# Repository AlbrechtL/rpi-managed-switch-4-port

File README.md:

# 4-Port Managed Switch

An open-source 4-port gigabit managed switch HAT based on a Raspberry Pi with OpenWrt support.

**Disclaimer:** This is an ongoing project where some features are not working, and some hardware bugs may exist.

## Features
* 4 Gigabit Ethernet RJ45 ports  
* Supports Raspberry Pi 1–5 (including Raspberry Pi Zero 1–2)  
  - Tested with a Raspberry Pi Zero 1  
  - Raspberry Pi 5 is not working with OpenWrt due to this [issue](https://github.com/openwrt/openwrt/issues/18034)  
* Works with a [custom OpenWrt](https://github.com/AlbrechtL/rpi-managed-switch-openwrt/tree/rpi_managed_switch)  
* Supported by Linux [Distributed Switch Architecture (DSA)](https://www.kernel.org/doc/Documentation/networking/dsa/dsa.txt)  
* VLAN support
* Switching hardware offloading support 
* Hardware design in KiCad
* Ready for JLCPCB production
  - Using a much as possible basic parts to lower the assembling costs

## Software Status

The hardware works with a adapted OpenWrt: https://github.com/AlbrechtL/openwrt/tree/rpi_managed_switch

I added the following to OpenWrt:  
* Device tree overlays for DSA
* Enabled the ENC28J60 driver 
* Added a small patch to enable the ENC28J60 for DSA  
* Added detection of DSA in the first boot scripts so that OpenWrt uses the switch  

See the differences:  
https://github.com/openwrt/openwrt/compare/main...AlbrechtL:openwrt:rpi_managed_switch  

Communication with the RTL8367S switch chip uses Linux DSA. There is also an OpenWrt-specific driver (`drivers/net/phy/rtl8367b.c`) for OpenWrt's legacy `swconfig` framework, but since OpenWrt is moving to DSA, it does not make sense to use it in this project. That said, this driver does work with this switch.

**Distributed Switch Architecture (DSA)**

The to go Linux driver is: `drivers/net/dsa/realtek/rtl8365mb.c`
* Key aspects:
  - Integrated into the Linux kernel  
  - Mainline RTL8367S support  
  - Works on Raspberry Pi OS with a custom Linux kernel
  - Actively maintained
  - Hardware offloading and VLAN support
    - May be added into Linux 7.2 (https://lore.kernel.org/all/20260606-realtek_forward-v13-0-b9e409687cbe@gmail.com/)
    - Available in mainline OpenWrt (https://github.com/openwrt/openwrt/pull/23738)

DSA Example:
```
root@OpenWrt:~# ip addr
1: lo: <LOOPBACK,UP,LOWER_UP> mtu 65536 qdisc noqueue state UNKNOWN qlen 1000
    link/loopback 00:00:00:00:00:00 brd 00:00:00:00:00:00
    inet 127.0.0.1/8 scope host lo
       valid_lft forever preferred_lft forever
    inet6 ::1/128 scope host 
       valid_lft forever preferred_lft forever
2: eth0: <BROADCAST,MULTICAST,UP,LOWER_UP> mtu 1508 qdisc fq_codel state UP qlen 1000
    link/ether b8:27:eb:8f:43:df brd ff:ff:ff:ff:ff:ff
    inet6 fe80::ba27:ebff:fe8f:43df/64 scope link 
       valid_lft forever preferred_lft forever
3: lan1@eth0: <BROADCAST,MULTICAST,UP,LOWER_UP> mtu 1500 qdisc noqueue master switch state UP qlen 1000
    link/ether b8:27:eb:8f:43:df brd ff:ff:ff:ff:ff:ff
4: lan2@eth0: <NO-CARRIER,BROADCAST,MULTICAST,UP> mtu 1500 qdisc noqueue master switch state DOWN qlen 1000
    link/ether b8:27:eb:8f:43:e0 brd ff:ff:ff:ff:ff:ff
5: lan3@eth0: <NO-CARRIER,BROADCAST,MULTICAST,UP> mtu 1500 qdisc noqueue master switch state DOWN qlen 1000
    link/ether b8:27:eb:8f:43:e1 brd ff:ff:ff:ff:ff:ff
6: lan4@eth0: <BROADCAST,MULTICAST,UP,LOWER_UP> mtu 1500 qdisc noqueue master switch state UP qlen 1000
    link/ether b8:27:eb:8f:43:e2 brd ff:ff:ff:ff:ff:ff
7: switch: <BROADCAST,MULTICAST,UP,LOWER_UP> mtu 1500 qdisc noqueue state UP qlen 1000
    link/ether b8:27:eb:8f:43:df brd ff:ff:ff:ff:ff:ff
    inet6 fe80::ba27:ebff:fe8f:43df/64 scope link 
       valid_lft forever preferred_lft forever
8: switch.1@switch: <BROADCAST,MULTICAST,UP,LOWER_UP> mtu 1500 qdisc noqueue state UP qlen 1000
    link/ether b8:27:eb:8f:43:df brd ff:ff:ff:ff:ff:ff
    inet 192.168.1.1/24 brd 192.168.1.255 scope global switch.1
       valid_lft forever preferred_lft forever
    inet6 fd8d:3fdb:486f::1/60 scope global noprefixroute 
       valid_lft forever preferred_lft forever
    inet6 fe80::ba27:ebff:fe8f:43df/64 scope link 
       valid_lft forever preferred_lft forever
```

OpenWrt DSA screenshot  

## Hardware Status

I have two assembled PCBs that have basic functionality. See [issues](https://github.com/AlbrechtL/rpi-managed-switch-4-port/issues) for a list of hardware problems.

**Raspberry Pi Zero**

**Raspberry Pi 5**

## Performance

I don't have detailed performance measurements yet, but here are some bandwidth indications:  
* **RJ45–RJ45 with DSA (rtl8365mb) and offloading patches:** ~1 Gbit/s (wire speed, full-duplex)   
* **RJ45–RJ45 with DSA (rtl8365mb):** ~2 Mbit/s  
  Currently, the RTL8367S DSA driver doesn't support hardware offloading. As a result, all traffic is routed through the Raspberry Pi and the very slow SPI interface. For a switch, this is not acceptable.  
* **Raspberry Pi to RJ45 (CPU port):** ~5 Mbit/s (half-duplex)  
  To support the inexpensive Raspberry Pi Zero, an external SPI Ethernet chip (ENC28J60) is used to connect to the main switch chip (RTL8367S). Due to the slow SPI interface, only ~5 Mbit/s can be achieved. However, for a managed web interface, that's sufficient.  

## Acknowledgements

I would like to thank the following open-source projects. Without these great works, this open-source switch would not be possible:  
* [OpenWrt](https://openwrt.org/)  
* RTL8367S Managed Switch  
  - Blog post: https://blog.brixit.nl/making-a-linux-managed-network-switch/  
  - KiCad: https://github.com/FOSDEM/video/tree/master/hardware/pcbs/switch_board  
* ENC28J60 on a Raspberry Pi Zero  
  - Hackster: https://www.hackster.io/lightside-instruments/the-ethernet4pizero-ethernet-for-raspberry-pi-zero-shield-dd4316  
  - KiCad: https://github.com/lightside-instruments/ethernet4pizero.git  
* [RPI5-CFE-Hat](https://github.com/will127534/RPI5-CFE-Hat)  
* [PCIe3_Hub](https://github.com/will127534/PCIe3_Hub)  
* [RouterPi](https://github.com/ZakKemble/RouterPi)

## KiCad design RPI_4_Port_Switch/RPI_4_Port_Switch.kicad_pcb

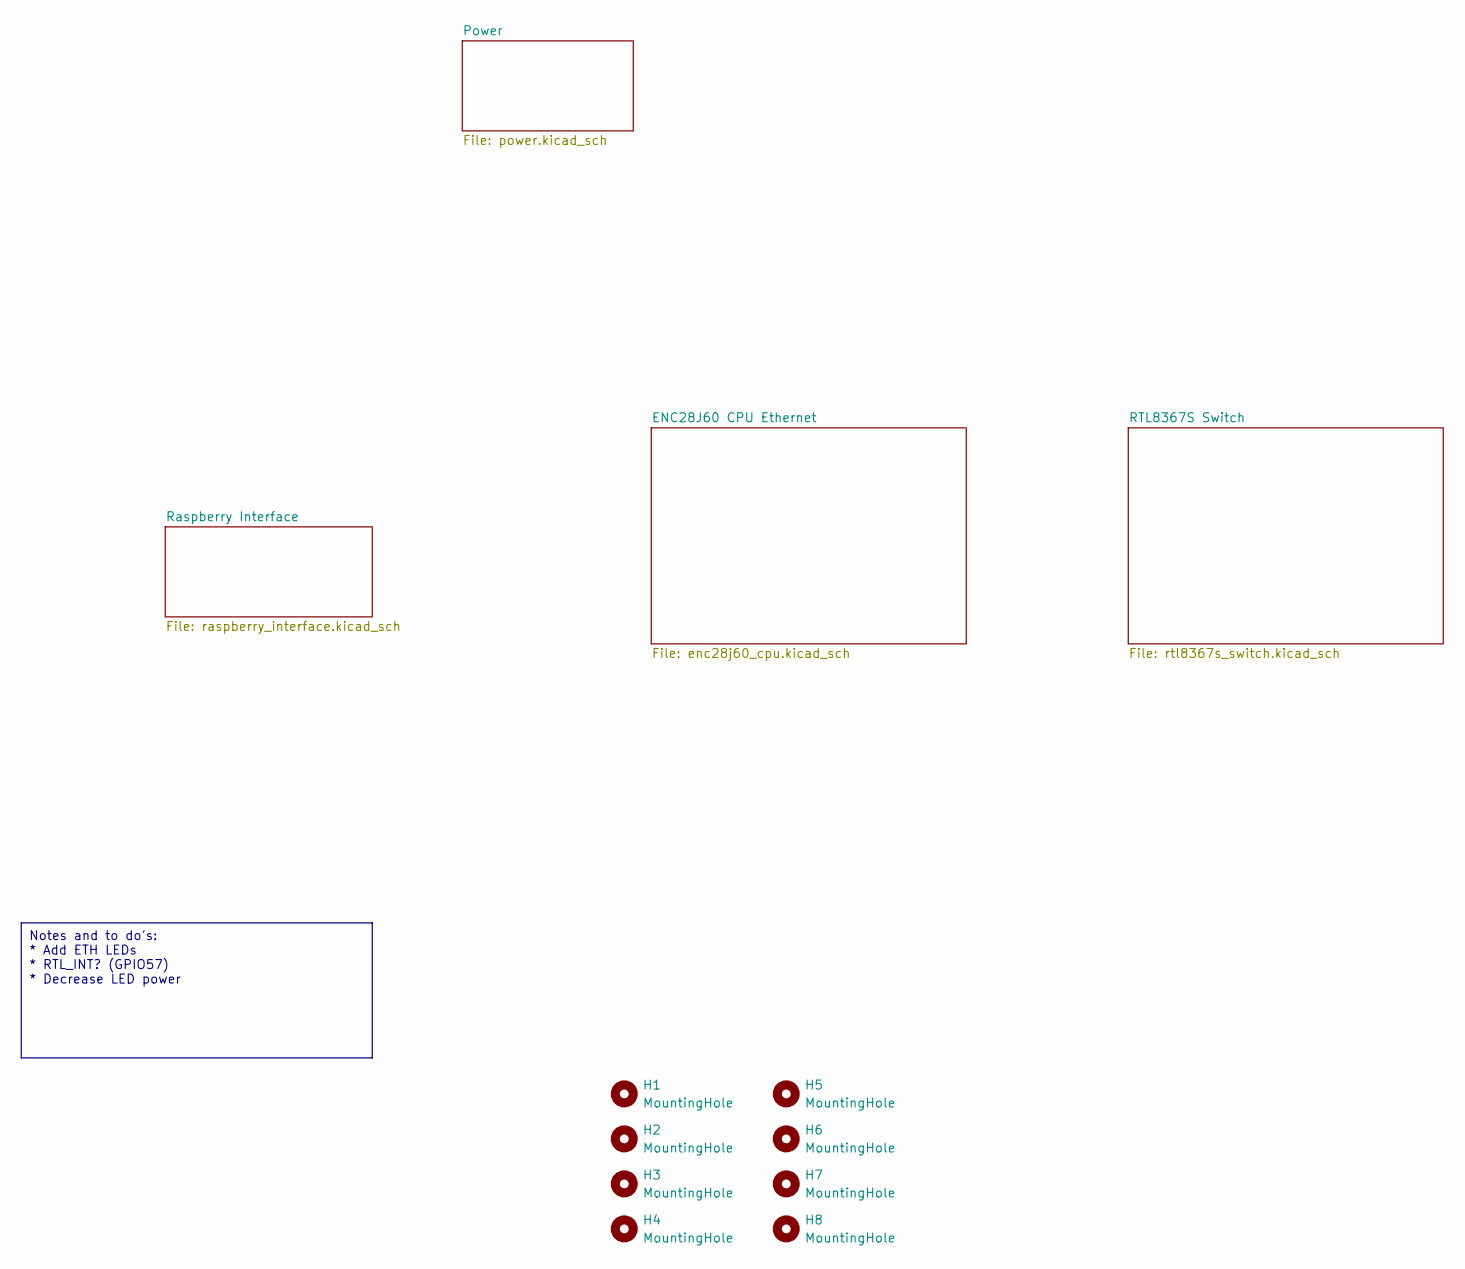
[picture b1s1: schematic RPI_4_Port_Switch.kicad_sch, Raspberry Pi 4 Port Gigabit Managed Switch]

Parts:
H1, H2, H3, H4, H5, H6, H7, H8: MountingHole; screw_hole

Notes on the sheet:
Notes and to do's: * Add ETH LEDs * RTL_INT? (GPIO57) * Decrease LED power

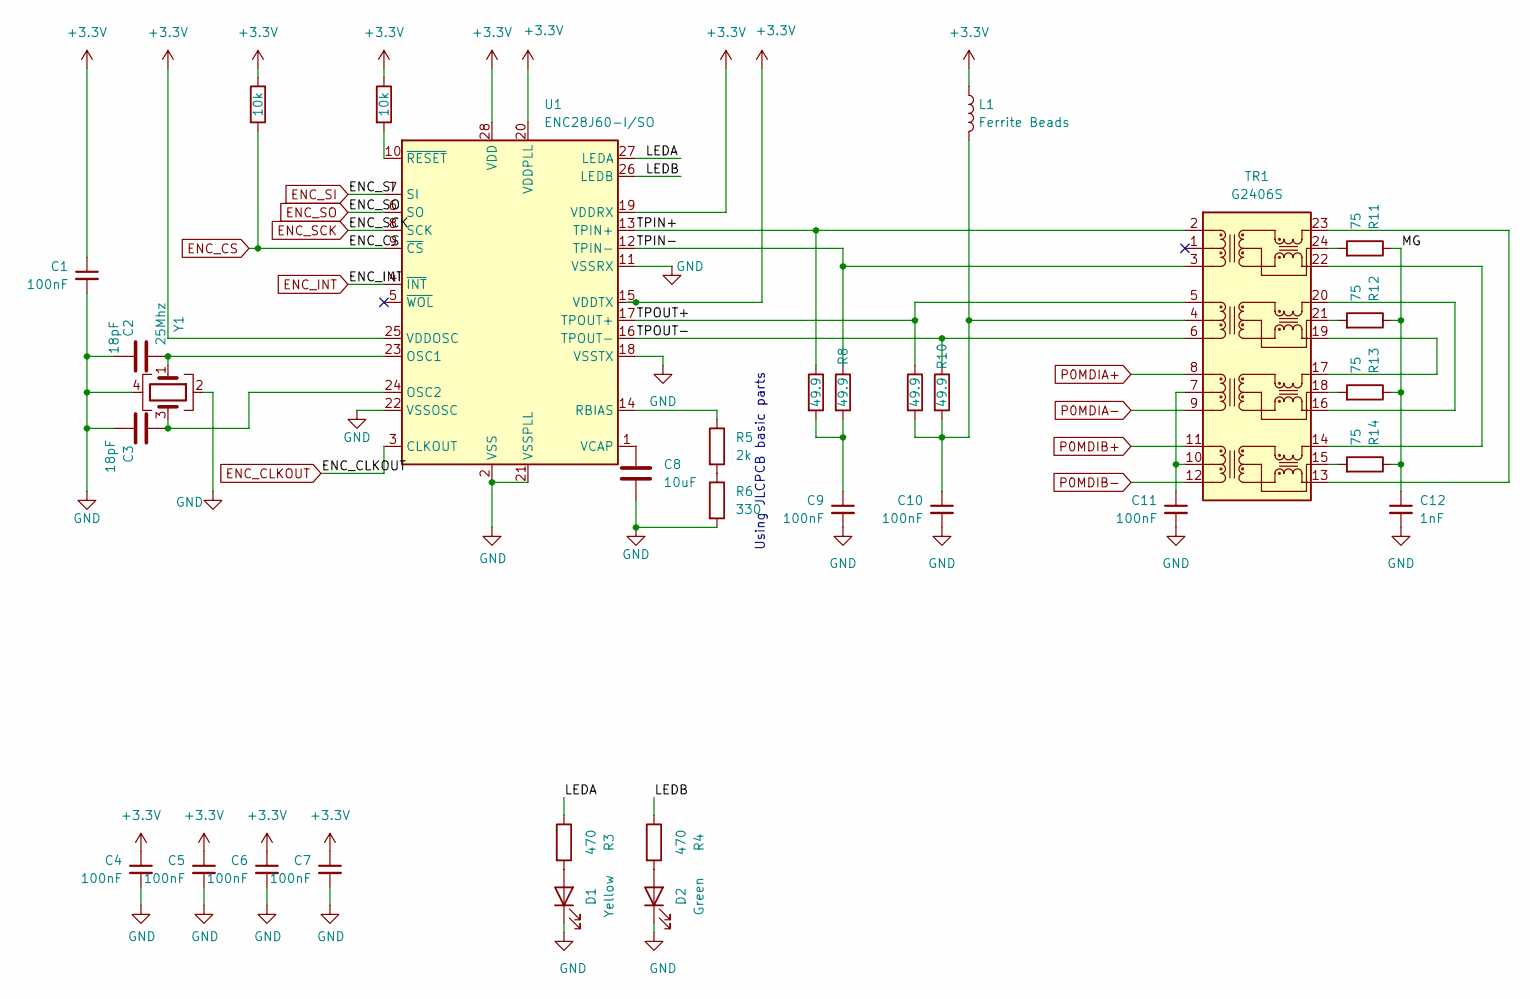
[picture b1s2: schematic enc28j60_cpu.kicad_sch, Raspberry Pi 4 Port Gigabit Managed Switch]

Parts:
C1, C4, C5, C6, C7, C9, C10, C11: 100nF; C_0603_1608Metric; Part 50V 100nF X7R ±10% 0603; LCSC Part # C14663
C2, C3: 18pF; C_0603_1608Metric; Part 50V 18pF C0G ±5% 0603; LCSC Part # C1647
C8: 10uF; C_0402_1005Metric; Part 6.3V 10uF X5R ±20% 0402; LCSC Part # C15525
C12: 1nF; C_0603_1608Metric; Part 50V 1nF X7R ±10% 0603; LCSC Part # C1588
D1: Yellow; LED_0805_2012Metric; Part Yellow 0805 LED Indication; LCSC Part # C2296
D2: Green; LED_0805_2012Metric; Part Emerald 0805 LED Indication (green); LCSC Part # C2297
L1: Ferrite Beads; L_0805_2012Metric; LCSC Part # C1015
R1, R2: 10k; R_1206_3216Metric; Part 250mW Thick Film Resistors 200V ±100ppm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; LCSC Part # C17902
R3, R4: 470; R_0402_1005Metric; Part 62.5mW Thick Film Resistors 50V ±100ppm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; LCSC Part # C25117
R5: 2k; R_0402_1005Metric; Part 62.5mW Thick Film Resistors 50V ±100ppm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; LCSC Part # C4109
R6: 330; R_0402_1005Metric; Part 62.5mW Thick Film Resistors 50V ±100ppm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; LCSC Part # C25104
R7, R8, R9, R10: 49.9; R_0402_1005Metric; Part 62.5mW Thick Film Resistors 50V ±100ppm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; LCSC Part # C25120
R11, R12, R13, R14: 75; R_0603_1608Metric; Part R 75Ω 125mW 1% 0603; LCSC Part # C4275
TR1: G2406S; Part G2406S; LCSC Part # C507595
U1: ENC28J60-I/SO; SOIC-28W_7.5x17.9mm_P1.27mm; LCSC Part # C47351
Y1: 25Mhz; Crystal_SMD_Abracon_ABM8G-4Pin_3.2x2.5mm; LCSC Part # C9006

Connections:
+3.3V: C1.1, C4.1, C5.1, C6.1, C7.1, L1.1, R1.1, R2.1, U1.15 (VDDTX), U1.19 (VDDRX), U1.20 (VDDPLL), U1.25 (VDDOSC), U1.28 (VDD); also elsewhere on the board
/ENC28J60 CPU Ethernet/LEDA: R3.1, U1.27 (LEDA)
/ENC28J60 CPU Ethernet/LEDB: R4.1, U1.26 (LEDB)
/ENC28J60 CPU Ethernet/MG: C12.1, R11.1, R12.1, R13.1, R14.1
/ENC28J60 CPU Ethernet/TPIN+: R7.1, TR1.2 (TD1+), U1.13 (TPIN+)
/ENC28J60 CPU Ethernet/TPIN-: R8.1, TR1.3 (TD1-), U1.12 (TPIN-)
/ENC28J60 CPU Ethernet/TPOUT+: R9.1, TR1.5 (TD2+), U1.17 (TPOUT+)
/ENC28J60 CPU Ethernet/TPOUT-: R10.1, TR1.6 (TD2-), U1.16 (TPOUT-)
ENC_CLKOUT: U1.3 (CLKOUT); also elsewhere on the board
ENC_CS: R1.2, U1.9 (~CS); also elsewhere on the board
ENC_INT: U1.4 (~INT); also elsewhere on the board
ENC_SCK: U1.8 (SCK); also elsewhere on the board
ENC_SI: U1.7 (SI); also elsewhere on the board
ENC_SO: U1.6 (SO); also elsewhere on the board
GND: C1.2, C2.2, C3.2, C4.2, C5.2, C6.2, C7.2, C8.2, C9.2, C10.2, C11.2, C12.2, D1.1 (K), D2.1 (K), R6.2, U1.2 (VSS), U1.11 (VSSRX), U1.18 (VSSTX), U1.21 (VSSPLL), U1.22 (VSSOSC), Y1.2, Y1.4; also elsewhere on the board
unnamed: C9.1, R7.2, R8.2
unnamed: C10.1, L1.2, R9.2, R10.2, TR1.4 (CT)
unnamed: C11.1, TR1.7 (CT), TR1.10 (CT)
unnamed: D1.2 (A), R3.2
unnamed: D2.2 (A), R4.2
unnamed: R5.2, R6.1
unnamed: R11.2, TR1.24 (CT)
unnamed: R12.2, TR1.21 (CT)
unnamed: R13.2, TR1.18 (CT)
unnamed: R14.2, TR1.15 (CT)
unnamed: TR1.13 (MX4-), TR1.23 (MX1+)
unnamed: TR1.14 (MX4+), TR1.22 (MX1-)
unnamed: TR1.16 (MX3-), TR1.20 (MX2+)
unnamed: TR1.17 (MX3+), TR1.19 (MX2-)
unnamed: C2.1, U1.23 (OSC1), Y1.1
unnamed: C3.1, U1.24 (OSC2), Y1.3
unnamed: R5.1, U1.14 (RBIAS)
unnamed: C8.1, U1.1 (VCAP)
unnamed: R2.2, U1.10 (~RESET)
P0MDIA+: TR1.8 (TD3+); also elsewhere on the board
P0MDIA-: TR1.9 (TD3-); also elsewhere on the board
P0MDIB+: TR1.11 (TD4+); also elsewhere on the board
P0MDIB-: TR1.12 (TD4-); also elsewhere on the board

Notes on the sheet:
Using JLCPCB basic parts

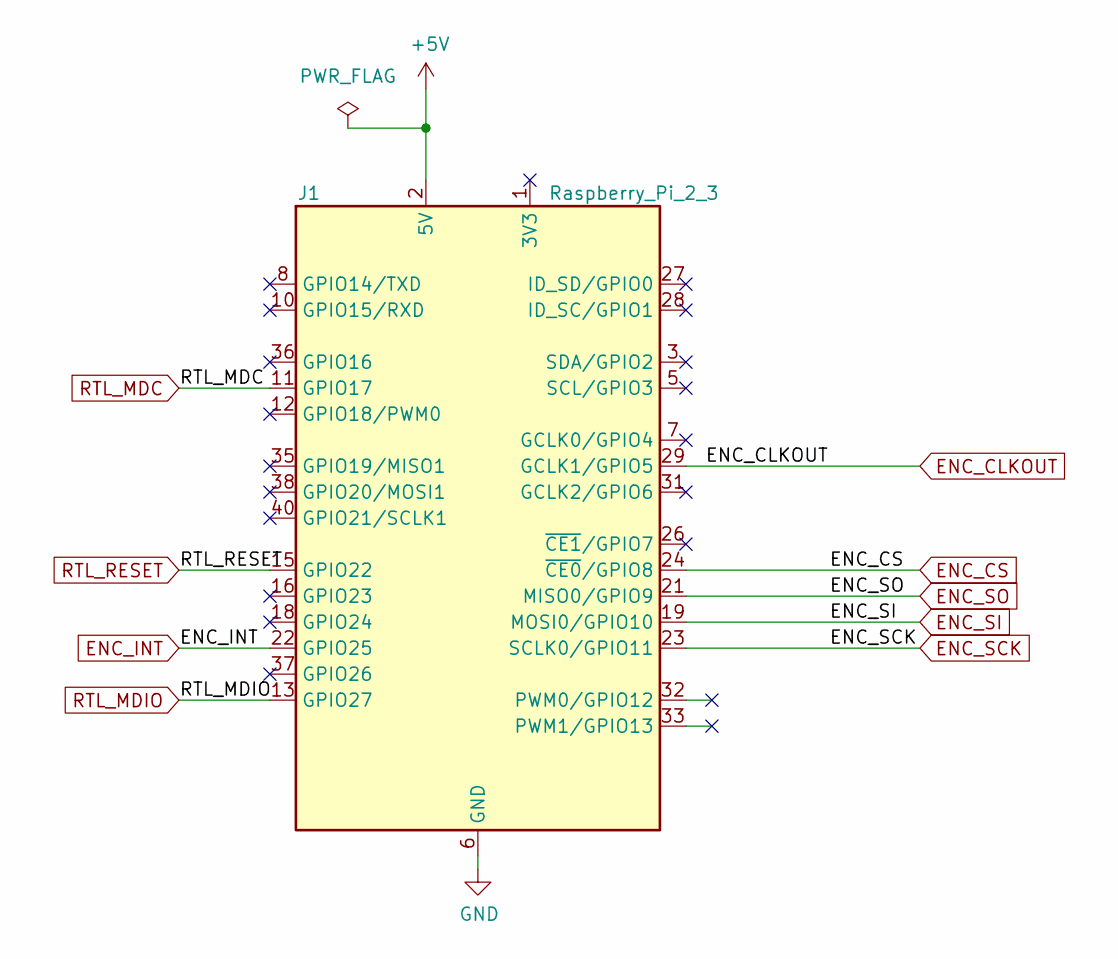
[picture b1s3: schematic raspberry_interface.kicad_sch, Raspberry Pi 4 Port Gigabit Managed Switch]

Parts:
J1: Raspberry_Pi_2_3; PinSocket_2x20_P2.54mm_Vertical_1_04mm

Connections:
+5V: J1.2 (5V), J1.4 (5V); also elsewhere on the board
ENC_CLKOUT: J1.29 (GCLK1/GPIO5); also elsewhere on the board
ENC_CS: J1.24 (~CE0/GPIO8); also elsewhere on the board
ENC_INT: J1.22 (GPIO25); also elsewhere on the board
ENC_SCK: J1.23 (SCLK0/GPIO11); also elsewhere on the board
ENC_SI: J1.19 (MOSI0/GPIO10); also elsewhere on the board
ENC_SO: J1.21 (MISO0/GPIO9); also elsewhere on the board
GND: J1.6 (GND), J1.9 (GND), J1.14 (GND), J1.20 (GND), J1.25 (GND), J1.30 (GND), J1.34 (GND), J1.39 (GND); also elsewhere on the board
RTL_MDC: J1.11 (GPIO17); also elsewhere on the board
RTL_MDIO: J1.13 (GPIO27); also elsewhere on the board
RTL_RESET: J1.15 (GPIO22); also elsewhere on the board

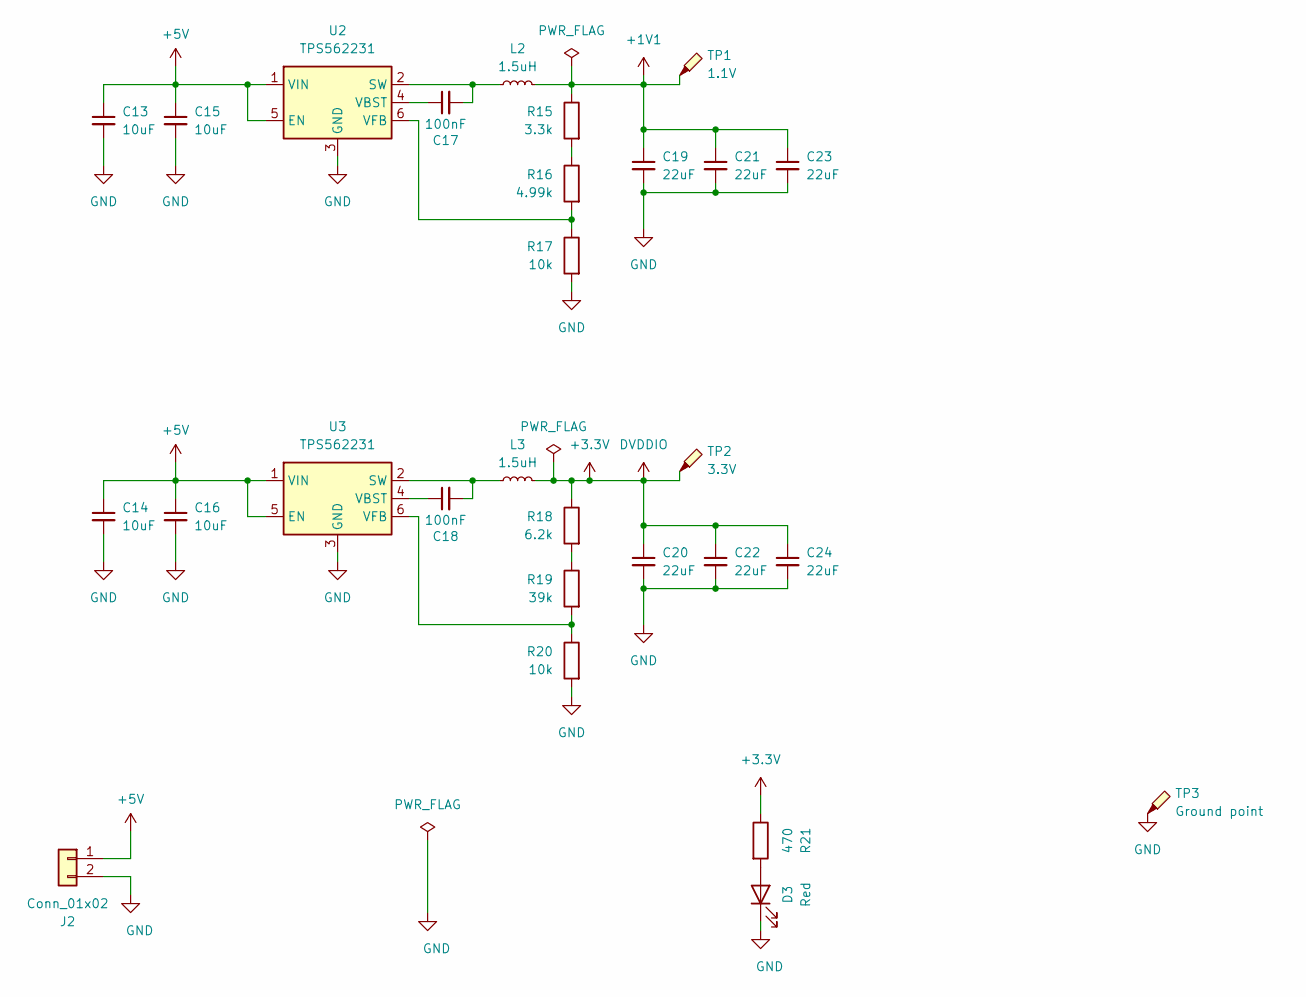
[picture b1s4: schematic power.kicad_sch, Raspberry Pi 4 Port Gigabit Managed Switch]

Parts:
C13, C14, C15, C16: 10uF; C_0402_1005Metric; Part 6.3V 10uF X5R ±20% 0402; LCSC Part # C15525
C17, C18: 100nF; C_0603_1608Metric; Part 50V 100nF X7R ±10% 0603; LCSC Part # C14663
C19, C20, C21, C22, C23, C24: 22uF; C_0603_1608Metric; Part 6.3V 22uF X5R ±20% 0603; LCSC Part # C59461
D3: Red; LED_0603_1608Metric; Part LED Red 0603; LCSC Part # C2286
J2: Conn_01x02; PinSocket_1x02_P2.54mm_Vertical
L2, L3: 1.5uH; L_Taiyo-Yuden_MD-5050; Part BWVF005050201R5T00 or 74404054015; LCSC Part # C702825
R15: 3.3k; R_0603_1608Metric; Part R 3.3kΩ 125mW 1% 0603; LCSC Part # C22978
R16: 4.99k; R_0603_1608Metric; Part R 4.99kΩ 125mW 1% 0603; LCSC Part # C23046
R17, R20: 10k; R_1206_3216Metric; Part 250mW Thick Film Resistors 200V ±100ppm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; LCSC Part # C17902
R18: 6.2k; R_0603_1608Metric; Part R 6.2kΩ 125mW 1% 0603; LCSC Part # C4260
R19: 39k; R_0603_1608Metric; Part R 39kΩ 125mW 1% 0603; LCSC Part # C23153
R21: 470; R_0402_1005Metric; Part 62.5mW Thick Film Resistors 50V ±100ppm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; LCSC Part # C25117
TP1: 1.1V; TestPoint_THTPad_2.0x2.0mm_Drill1.0mm
TP2: 3.3V; TestPoint_THTPad_2.0x2.0mm_Drill1.0mm
TP3: Ground point; TestPoint_Bridge_Pitch2.54mm_Drill1.0mm
U2, U3: TPS562231; SOT-563; Part TPS562231DRLR; LCSC Part # C2070899

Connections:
+1V1: C19.1, C21.1, C23.1, L2.2, R15.1, TP1.1; also elsewhere on the board
+3.3V: C20.1, C22.1, C24.1, L3.2, R18.1, R21.1, TP2.1; also elsewhere on the board
+5V: C13.1, C14.1, C15.1, C16.1, J2.1, U2.1 (VIN), U2.5 (EN), U3.1 (VIN), U3.5 (EN); also elsewhere on the board
GND: C13.2, C14.2, C15.2, C16.2, C19.2, C20.2, C21.2, C22.2, C23.2, C24.2, D3.1 (K), J2.2, R17.2, R20.2, TP3.1, U2.3 (GND), U3.3 (GND); also elsewhere on the board
unnamed: D3.2 (A), R21.2
unnamed: R15.2, R16.1
unnamed: R18.2, R19.1
unnamed: C17.2, L2.1, U2.2 (SW)
unnamed: C17.1, U2.4 (VBST)
unnamed: R16.2, R17.1, U2.6 (VFB)
unnamed: C18.2, L3.1, U3.2 (SW)
unnamed: C18.1, U3.4 (VBST)
unnamed: R19.2, R20.1, U3.6 (VFB)

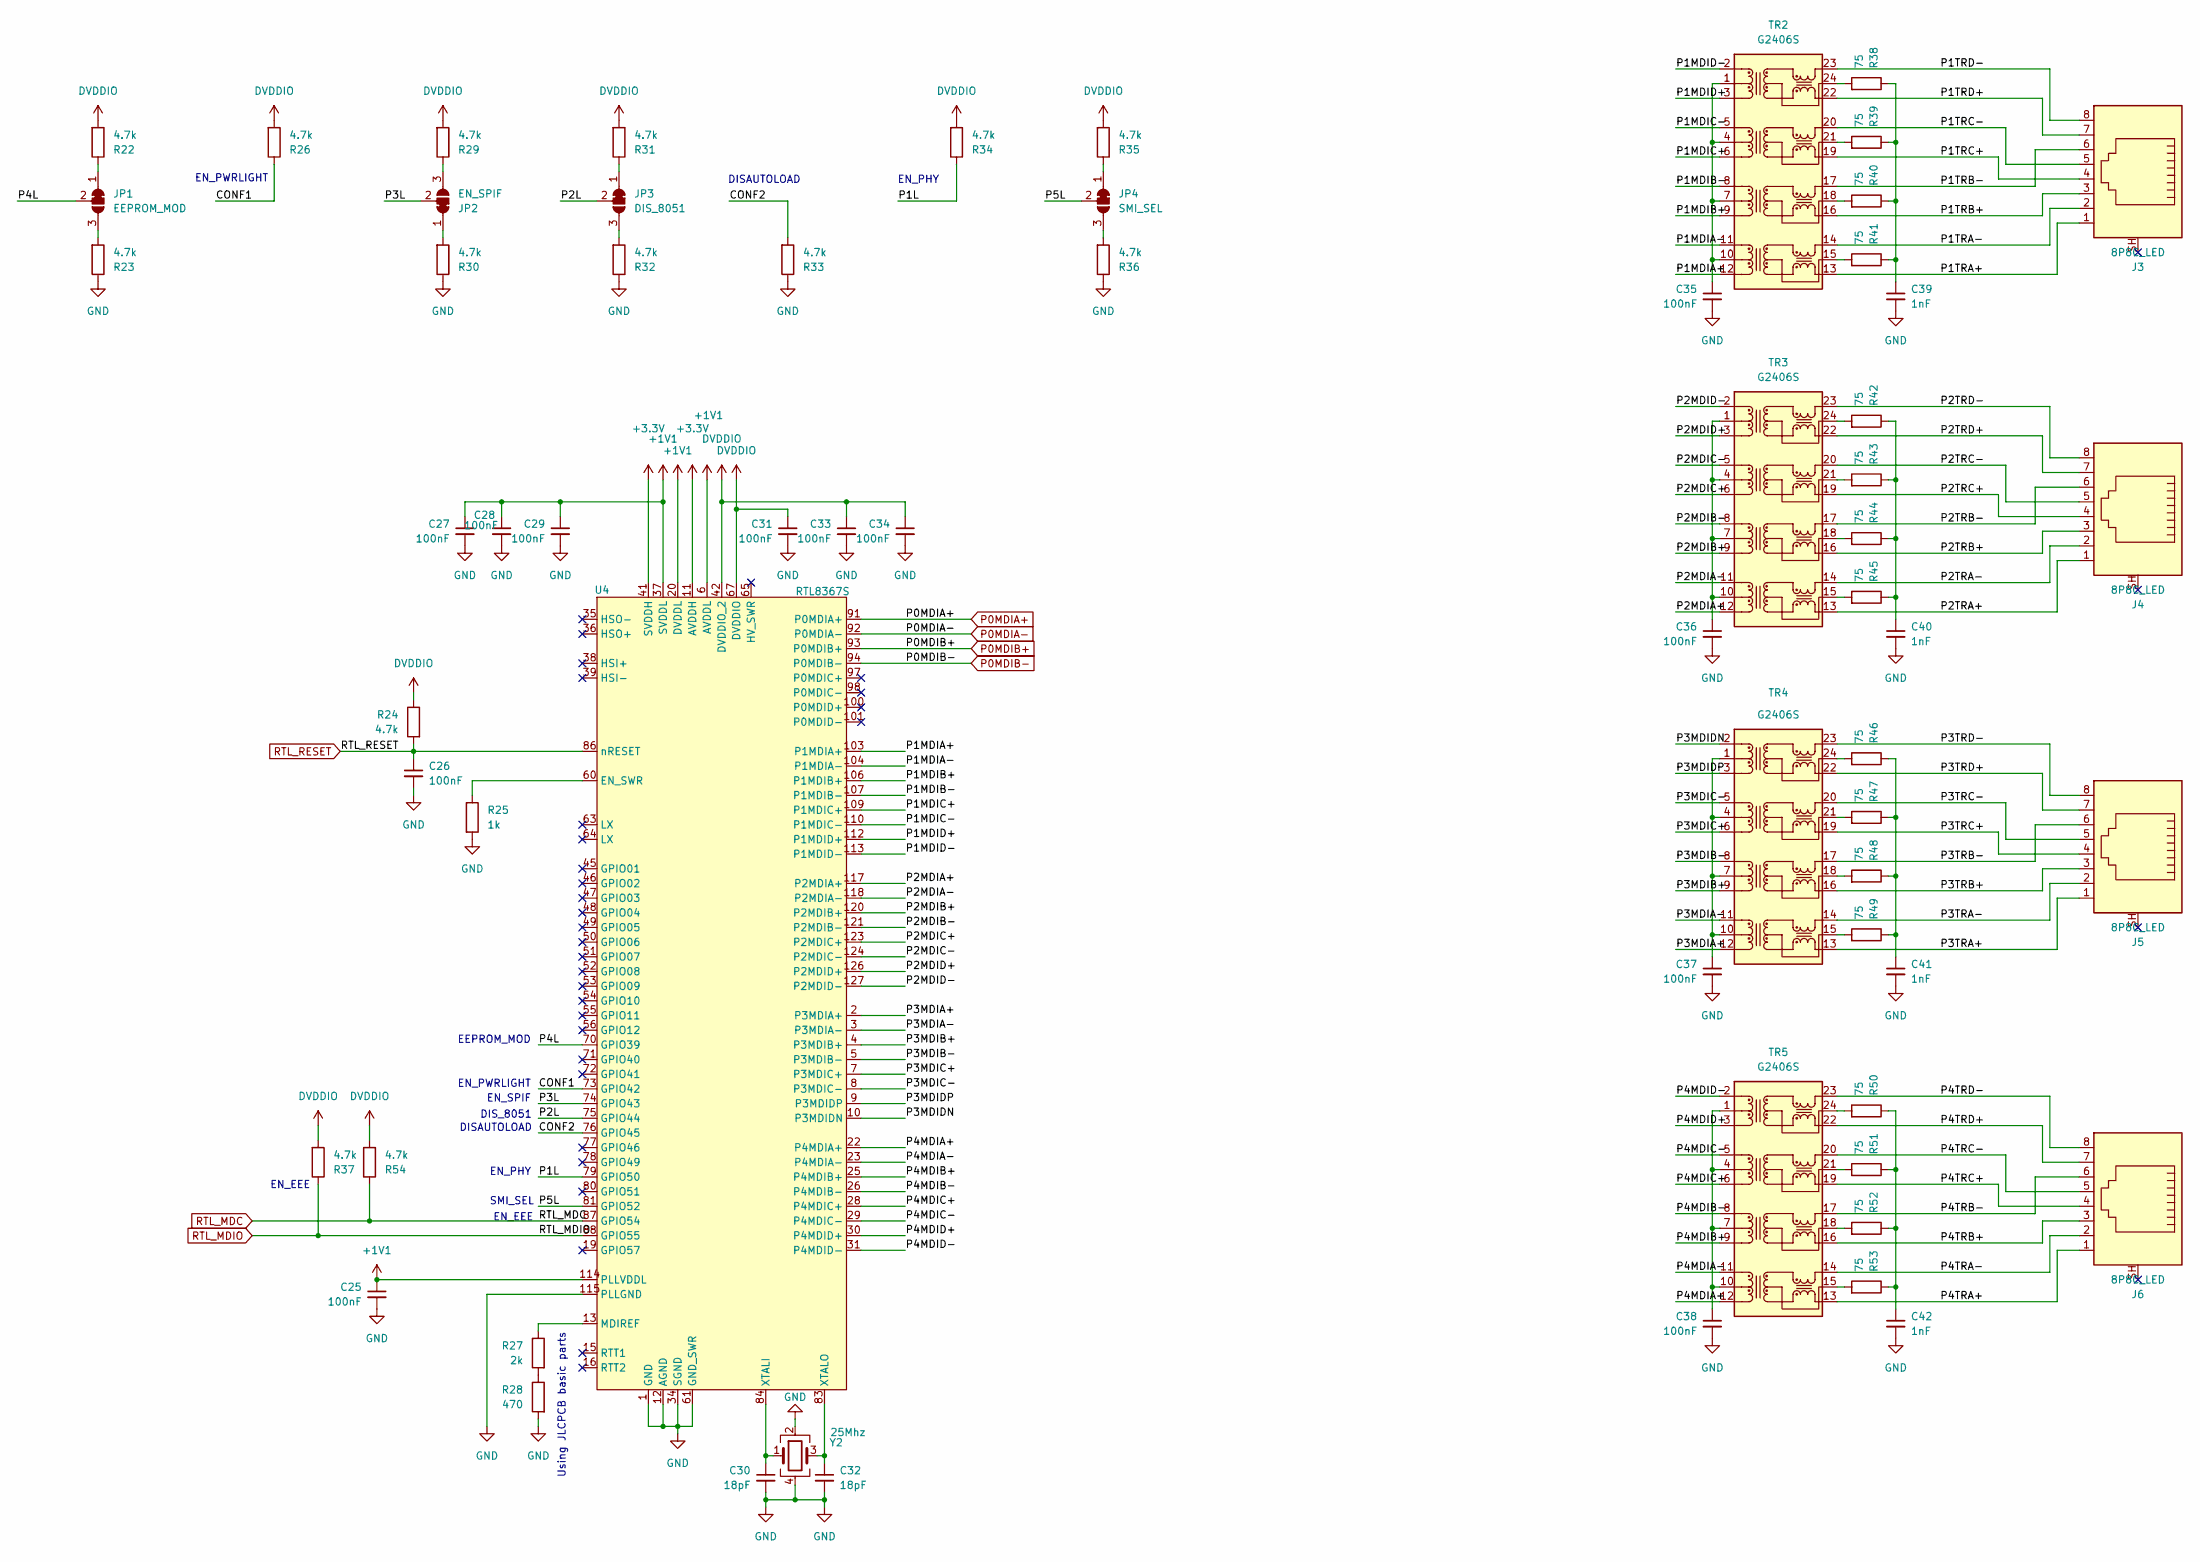
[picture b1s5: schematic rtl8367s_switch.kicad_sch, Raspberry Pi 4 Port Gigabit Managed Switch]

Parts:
C25, C26, C27, C28, C29, C31, C33, C34, C35, C36, C37, C38: 100nF; C_0603_1608Metric; Part 50V 100nF X7R ±10% 0603; LCSC Part # C14663
C30, C32: 18pF; C_0603_1608Metric; Part 50V 18pF C0G ±5% 0603; LCSC Part # C1647
C39, C40, C41, C42: 1nF; C_0603_1608Metric; Part 50V 1nF X7R ±10% 0603; LCSC Part # C1588
J3, J4, J5, J6: 8P8C_LED; Heling MJ88-B211-JRS3; Part MJ88-B211-JRS3; LCSC Part # C2895614
JP1: EEPROM_MOD; SolderJumper-3_P1.3mm_Bridged12_RoundedPad1.0x1.5mm
JP2: EN_SPIF; SolderJumper-3_P1.3mm_Bridged12_RoundedPad1.0x1.5mm
JP3: DIS_8051; SolderJumper-3_P1.3mm_Bridged12_RoundedPad1.0x1.5mm
JP4: SMI_SEL; SolderJumper-3_P1.3mm_Bridged12_RoundedPad1.0x1.5mm
R22, R23, R24, R26, R29, R30, R31, R32, R33, R34, R35, R36, R37, R54: 4.7k; R_0402_1005Metric; LCSC Part # C25900
R25: 1k; R_0603_1608Metric; Part R 1kΩ 125mW 1% 0603; LCSC Part # C21190
R27: 2k; R_0402_1005Metric; Part 62.5mW Thick Film Resistors 50V ±100ppm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; LCSC Part # C4109
R28: 470; R_0402_1005Metric; Part 62.5mW Thick Film Resistors 50V ±100ppm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; LCSC Part # C25117
R38, R39, R40, R41, R42, R43, R44, R45, R46, R47, R48, R49, R50, R51, R52, R53: 75; R_0603_1608Metric; Part R 75Ω 125mW 1% 0603; LCSC Part # C4275
TR2, TR3, TR4, TR5: G2406S; Part G2406S; LCSC Part # C507595
U4: RTL8367S; LQFP-128_14x14mm_P0.4mm; Part RTL8367S; LCSC Part # C2760849
Y2: 25Mhz; Crystal_SMD_Abracon_ABM8G-4Pin_3.2x2.5mm; LCSC Part # C9006

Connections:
+1V1: C25.1, C27.1, C28.1, C29.1, U4.6 (AVDDL), U4.14 (AVDDL), U4.20 (DVDDL), U4.27 (AVDDL), U4.37 (SVDDL), U4.58 (DVDDL), U4.69 (DVDDL), U4.95 (AVDDL), U4.108 (AVDDL), U4.114 (PLLVDDL), U4.122 (AVDDL); also elsewhere on the board
+3.3V: C31.1, C33.1, C34.1, R22.2, R24.1, R26.2, R29.2, R31.2, R34.2, R35.2, R37.2, R54.2, U4.11 (AVDDH), U4.17 (AVDDH), U4.21 (AVDDH), U4.33 (AVDDH), U4.41 (SVDDH), U4.42 (DVDDIO_2), U4.59 (DVDDIO_2), U4.67 (DVDDIO), U4.82 (AVDDH), U4.90 (AVDDH), U4.102 (AVDDH), U4.116 (AVDDH), U4.128 (AVDDH); also elsewhere on the board
/RTL8367S Switch/CONF1: R26.1, U4.73 (GPIO42)
/RTL8367S Switch/CONF2: R33.2, U4.76 (GPIO45)
/RTL8367S Switch/P1L: R34.1, U4.79 (GPIO50)
/RTL8367S Switch/P1MDIA+: TR2.12 (TD4-), U4.103 (P1MDIA+)
/RTL8367S Switch/P1MDIA-: TR2.11 (TD4+), U4.104 (P1MDIA-)
/RTL8367S Switch/P1MDIB+: TR2.9 (TD3-), U4.106 (P1MDIB+)
/RTL8367S Switch/P1MDIB-: TR2.8 (TD3+), U4.107 (P1MDIB-)
/RTL8367S Switch/P1MDIC+: TR2.6 (TD2-), U4.109 (P1MDIC+)
/RTL8367S Switch/P1MDIC-: TR2.5 (TD2+), U4.110 (P1MDIC-)
/RTL8367S Switch/P1MDID+: TR2.3 (TD1-), U4.112 (P1MDID+)
/RTL8367S Switch/P1MDID-: TR2.2 (TD1+), U4.113 (P1MDID-)
/RTL8367S Switch/P1TRA+: J3.1, TR2.13 (MX4-)
/RTL8367S Switch/P1TRA-: J3.2, TR2.14 (MX4+)
/RTL8367S Switch/P1TRB+: J3.3, TR2.16 (MX3-)
/RTL8367S Switch/P1TRB-: J3.6, TR2.17 (MX3+)
/RTL8367S Switch/P1TRC+: J3.4, TR2.19 (MX2-)
/RTL8367S Switch/P1TRC-: J3.5, TR2.20 (MX2+)
/RTL8367S Switch/P1TRD+: J3.7, TR2.22 (MX1-)
/RTL8367S Switch/P1TRD-: J3.8, TR2.23 (MX1+)
/RTL8367S Switch/P2L: JP3.2 (C), U4.75 (GPIO44)
/RTL8367S Switch/P2MDIA+: TR3.12 (TD4-), U4.117 (P2MDIA+)
/RTL8367S Switch/P2MDIA-: TR3.11 (TD4+), U4.118 (P2MDIA-)
/RTL8367S Switch/P2MDIB+: TR3.9 (TD3-), U4.120 (P2MDIB+)
/RTL8367S Switch/P2MDIB-: TR3.8 (TD3+), U4.121 (P2MDIB-)
/RTL8367S Switch/P2MDIC+: TR3.6 (TD2-), U4.123 (P2MDIC+)
/RTL8367S Switch/P2MDIC-: TR3.5 (TD2+), U4.124 (P2MDIC-)
/RTL8367S Switch/P2MDID+: TR3.3 (TD1-), U4.126 (P2MDID+)
/RTL8367S Switch/P2MDID-: TR3.2 (TD1+), U4.127 (P2MDID-)
/RTL8367S Switch/P2TRA+: J4.1, TR3.13 (MX4-)
/RTL8367S Switch/P2TRA-: J4.2, TR3.14 (MX4+)
/RTL8367S Switch/P2TRB+: J4.3, TR3.16 (MX3-)
/RTL8367S Switch/P2TRB-: J4.6, TR3.17 (MX3+)
/RTL8367S Switch/P2TRC+: J4.4, TR3.19 (MX2-)
/RTL8367S Switch/P2TRC-: J4.5, TR3.20 (MX2+)
/RTL8367S Switch/P2TRD+: J4.7, TR3.22 (MX1-)
/RTL8367S Switch/P2TRD-: J4.8, TR3.23 (MX1+)
/RTL8367S Switch/P3L: JP2.2 (C), U4.74 (GPIO43)
/RTL8367S Switch/P3MDIA+: TR4.12 (TD4-), U4.2 (P3MDIA+)
/RTL8367S Switch/P3MDIA-: TR4.11 (TD4+), U4.3 (P3MDIA-)
/RTL8367S Switch/P3MDIB+: TR4.9 (TD3-), U4.4 (P3MDIB+)
/RTL8367S Switch/P3MDIB-: TR4.8 (TD3+), U4.5 (P3MDIB-)
/RTL8367S Switch/P3MDIC+: TR4.6 (TD2-), U4.7 (P3MDIC+)
/RTL8367S Switch/P3MDIC-: TR4.5 (TD2+), U4.8 (P3MDIC-)
/RTL8367S Switch/P3MDIDN: TR4.2 (TD1+), U4.10 (P3MDIDN)
/RTL8367S Switch/P3MDIDP: TR4.3 (TD1-), U4.9 (P3MDIDP)
/RTL8367S Switch/P3TRA+: J5.1, TR4.13 (MX4-)
/RTL8367S Switch/P3TRA-: J5.2, TR4.14 (MX4+)
/RTL8367S Switch/P3TRB+: J5.3, TR4.16 (MX3-)
/RTL8367S Switch/P3TRB-: J5.6, TR4.17 (MX3+)
/RTL8367S Switch/P3TRC+: J5.4, TR4.19 (MX2-)
/RTL8367S Switch/P3TRC-: J5.5, TR4.20 (MX2+)
/RTL8367S Switch/P3TRD+: J5.7, TR4.22 (MX1-)
/RTL8367S Switch/P3TRD-: J5.8, TR4.23 (MX1+)
/RTL8367S Switch/P4L: JP1.2 (C), U4.70 (GPIO39)
/RTL8367S Switch/P4MDIA+: TR5.12 (TD4-), U4.22 (P4MDIA+)
/RTL8367S Switch/P4MDIA-: TR5.11 (TD4+), U4.23 (P4MDIA-)
/RTL8367S Switch/P4MDIB+: TR5.9 (TD3-), U4.25 (P4MDIB+)
/RTL8367S Switch/P4MDIB-: TR5.8 (TD3+), U4.26 (P4MDIB-)
/RTL8367S Switch/P4MDIC+: TR5.6 (TD2-), U4.28 (P4MDIC+)
/RTL8367S Switch/P4MDIC-: TR5.5 (TD2+), U4.29 (P4MDIC-)
/RTL8367S Switch/P4MDID+: TR5.3 (TD1-), U4.30 (P4MDID+)
/RTL8367S Switch/P4MDID-: TR5.2 (TD1+), U4.31 (P4MDID-)
/RTL8367S Switch/P4TRA+: J6.1, TR5.13 (MX4-)
/RTL8367S Switch/P4TRA-: J6.2, TR5.14 (MX4+)
/RTL8367S Switch/P4TRB+: J6.3, TR5.16 (MX3-)
/RTL8367S Switch/P4TRB-: J6.6, TR5.17 (MX3+)
/RTL8367S Switch/P4TRC+: J6.4, TR5.19 (MX2-)
/RTL8367S Switch/P4TRC-: J6.5, TR5.20 (MX2+)
/RTL8367S Switch/P4TRD+: J6.7, TR5.22 (MX1-)
/RTL8367S Switch/P4TRD-: J6.8, TR5.23 (MX1+)
/RTL8367S Switch/P5L: JP4.2 (C), U4.81 (GPIO52)
GND: C25.2, C26.2, C27.2, C28.2, C29.2, C30.2, C31.2, C32.2, C33.2, C34.2, C35.2, C36.2, C37.2, C38.2, C39.2, C40.2, C41.2, C42.2, R23.1, R25.2, R28.2, R30.1, R32.1, R33.1, R36.1, U4.1 (GND), U4.12 (AGND), U4.18 (GND), U4.24 (GND), U4.32 (GND), U4.34 (SGND), U4.40 (SGND), U4.43 (GND), U4.44 (GND), U4.57 (GND), U4.61 (GND_SWR), U4.62 (GND_SWR), U4.68 (GND), U4.85 (GND), U4.89 (GND), U4.96 (GND), U4.99 (GND), U4.105 (GND), U4.111 (GND), U4.115 (PLLGND), U4.119 (GND), U4.125 (GND), Y2.2, Y2.4; also elsewhere on the board
unnamed: C35.1, TR2.1 (CT), TR2.4 (CT), TR2.7 (CT), TR2.10 (CT)
unnamed: C36.1, TR3.1 (CT), TR3.4 (CT), TR3.7 (CT), TR3.10 (CT)
unnamed: C37.1, TR4.1 (CT), TR4.4 (CT), TR4.7 (CT), TR4.10 (CT)
unnamed: C38.1, TR5.1 (CT), TR5.4 (CT), TR5.7 (CT), TR5.10 (CT)
unnamed: C39.1, R38.1, R39.1, R40.1, R41.1
unnamed: C40.1, R42.1, R43.1, R44.1, R45.1
unnamed: C41.1, R46.1, R47.1, R48.1, R49.1
unnamed: C42.1, R50.1, R51.1, R52.1, R53.1
unnamed: JP1.1 (A), R22.1
unnamed: JP1.3 (B), R23.2
unnamed: JP2.1 (A), R30.2
unnamed: JP2.3 (B), R29.1
unnamed: JP3.1 (A), R31.1
unnamed: JP3.3 (B), R32.2
unnamed: JP4.1 (A), R35.1
unnamed: JP4.3 (B), R36.2
unnamed: R27.2, R28.1
unnamed: R38.2, TR2.24 (CT)
unnamed: R39.2, TR2.21 (CT)
unnamed: R40.2, TR2.18 (CT)
unnamed: R41.2, TR2.15 (CT)
unnamed: R42.2, TR3.24 (CT)
unnamed: R43.2, TR3.21 (CT)
unnamed: R44.2, TR3.18 (CT)
unnamed: R45.2, TR3.15 (CT)
unnamed: R46.2, TR4.24 (CT)
unnamed: R47.2, TR4.21 (CT)
unnamed: R48.2, TR4.18 (CT)
unnamed: R49.2, TR4.15 (CT)
unnamed: R50.2, TR5.24 (CT)
unnamed: R51.2, TR5.21 (CT)
unnamed: R52.2, TR5.18 (CT)
unnamed: R53.2, TR5.15 (CT)
unnamed: R25.1, U4.60 (EN_SWR)
unnamed: R27.1, U4.13 (MDIREF)
unnamed: C30.1, U4.84 (XTALI), Y2.1
unnamed: C32.1, U4.83 (XTALO), Y2.3
P0MDIA+: U4.91 (P0MDIA+); also elsewhere on the board
P0MDIA-: U4.92 (P0MDIA-); also elsewhere on the board
P0MDIB+: U4.93 (P0MDIB+); also elsewhere on the board
P0MDIB-: U4.94 (P0MDIB-); also elsewhere on the board
RTL_MDC: R54.1, U4.87 (GPIO54); also elsewhere on the board
RTL_MDIO: R37.1, U4.88 (GPIO55); also elsewhere on the board
RTL_RESET: C26.1, R24.2, U4.86 (nRESET); also elsewhere on the board

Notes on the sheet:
DIS_8051
EN_EEE
EEPROM_MOD
Using JLCPCB basic parts
EN_PWRLIGHT
SMI_SEL
EN_SPIF
DISAUTOLOAD
EN_PHY

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
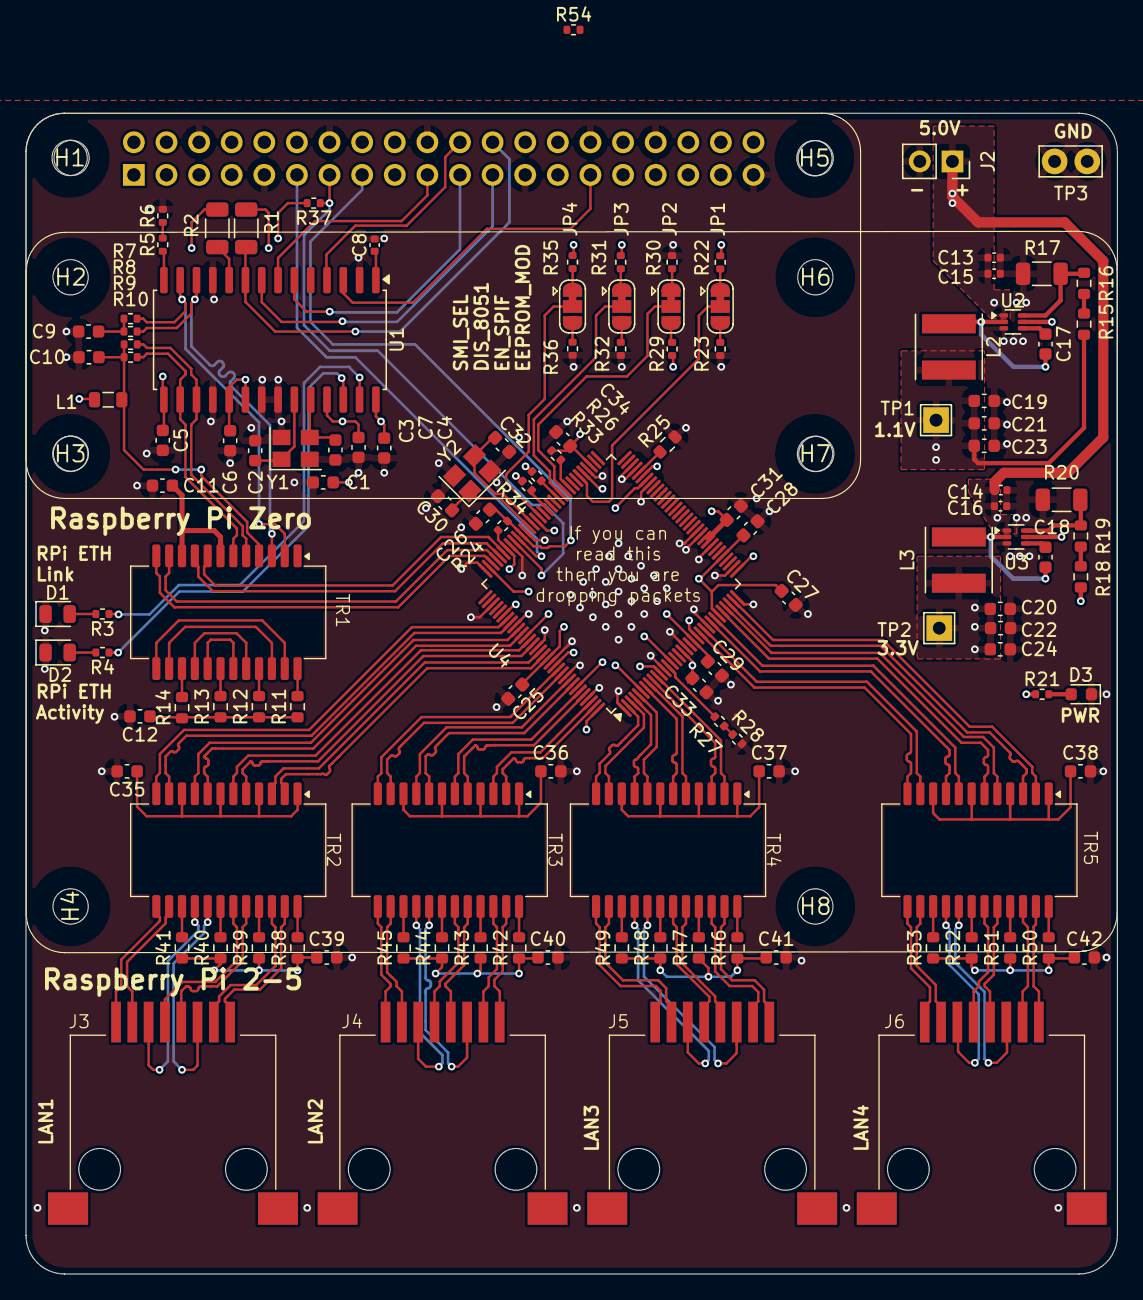
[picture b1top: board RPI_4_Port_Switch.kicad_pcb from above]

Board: 4 copper layers, 85.0 x 90.4 mm, 134 parts (1 on the bottom side), 160 nets.

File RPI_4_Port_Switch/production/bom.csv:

Designator,Footprint,Quantity,Value,LCSC Part #
"C1, C10, C11, C17, C18, C25, C26, C27, C28, C29, C31, C33, C34, C35, C36, C37, C38, C4, C5, C6, C7, C9",0603,22,100nF,C14663
"C12, C39, C40, C41, C42",0603,5,1nF,C1588
"C13, C14, C15, C16, C8",0402,5,10uF,C15525
"C19, C20, C21, C22, C23, C24",0603,6,22uF,C59461
"C2, C3, C30, C32",0603,4,18pF,C1647
D1,0805,1,Yellow,C2296
D2,0805,1,Green,C2297
D3,0603,1,Red,C2286
"H1, H2, H3, H4, H5, H6, H7, H8",screw_hole,8,MountingHole,
J1,PinSocket_2x20_P2.54mm_Vertical_1_04mm,1,Raspberry_Pi_2_3,
J2,PinSocket_1x02_P2.54mm_Vertical,1,Conn_01x02,
"J3, J4, J5, J6",Heling MJ88-B211-JRS3,4,8P8C_LED,C2895614
L1,0805,1,Ferrite Beads,C1015
"L2, L3",L_Taiyo-Yuden_MD-5050,2,1.5uH,C702825
"R1, R17, R2, R20",1206,4,10k,C17902
"R10, R7, R8, R9",0402,4,49.9,C25120
"R11, R12, R13, R14, R38, R39, R40, R41, R42, R43, R44, R45, R46, R47, R48, R49, R50, R51, R52, R53",0603,20,75,C4275
R15,0603,1,3.3k,C22978
R16,0603,1,4.99k,C23046
R18,0603,1,6.2k,C4260
R19,0603,1,39k,C23153
"R21, R28, R3, R4",0402,4,470,C25117
"R22, R23, R24, R26, R29, R30, R31, R32, R33, R34, R35, R36, R37",0402,13,4.7k,C25900
R25,0603,1,1k,C21190
"R27, R5",0402,2,2k,C4109
R6,0402,1,330,C25104
TP3,TestPoint_Bridge_Pitch2.54mm_Drill1.0mm,1,Ground point,
"TR1, TR2, TR3, TR4, TR5",G2406S,5,G2406S,C507595
U1,SOIC-28W_7.5x17.9mm_P1.27mm,1,ENC28J60-I/SO,C47351
"U2, U3",SOT-563,2,TPS562231,C2070899
U4,LQFP-128_14x14mm_P0.4mm,1,RTL8367S,C2760849
"Y1, Y2",Crystal_SMD_Abracon_ABM8G-4Pin_3.2x2.5mm,2,25Mhz,C9006

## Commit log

2025-03-03 Initial KiCAD project commit
2025-03-03 Initial readme content
2025-03-21 Add rtl8365mb-kernel-hacking link
2025-05-14 Add Raspberry Pi 5 picture
2025-08-01 Update DSA
2025-08-01 Update screenshot
2025-08-01 Update DSA screenshot text
2026-06-28 Update DSA section and remove obsolete OpenWrt swconfig.
